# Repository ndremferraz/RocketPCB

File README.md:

# RocketPCB
This repositiory is meant to store my individual work on the PCB for the GW Rocket Team. The code and other documentation is contained in the main repository for the GW Rocket Team

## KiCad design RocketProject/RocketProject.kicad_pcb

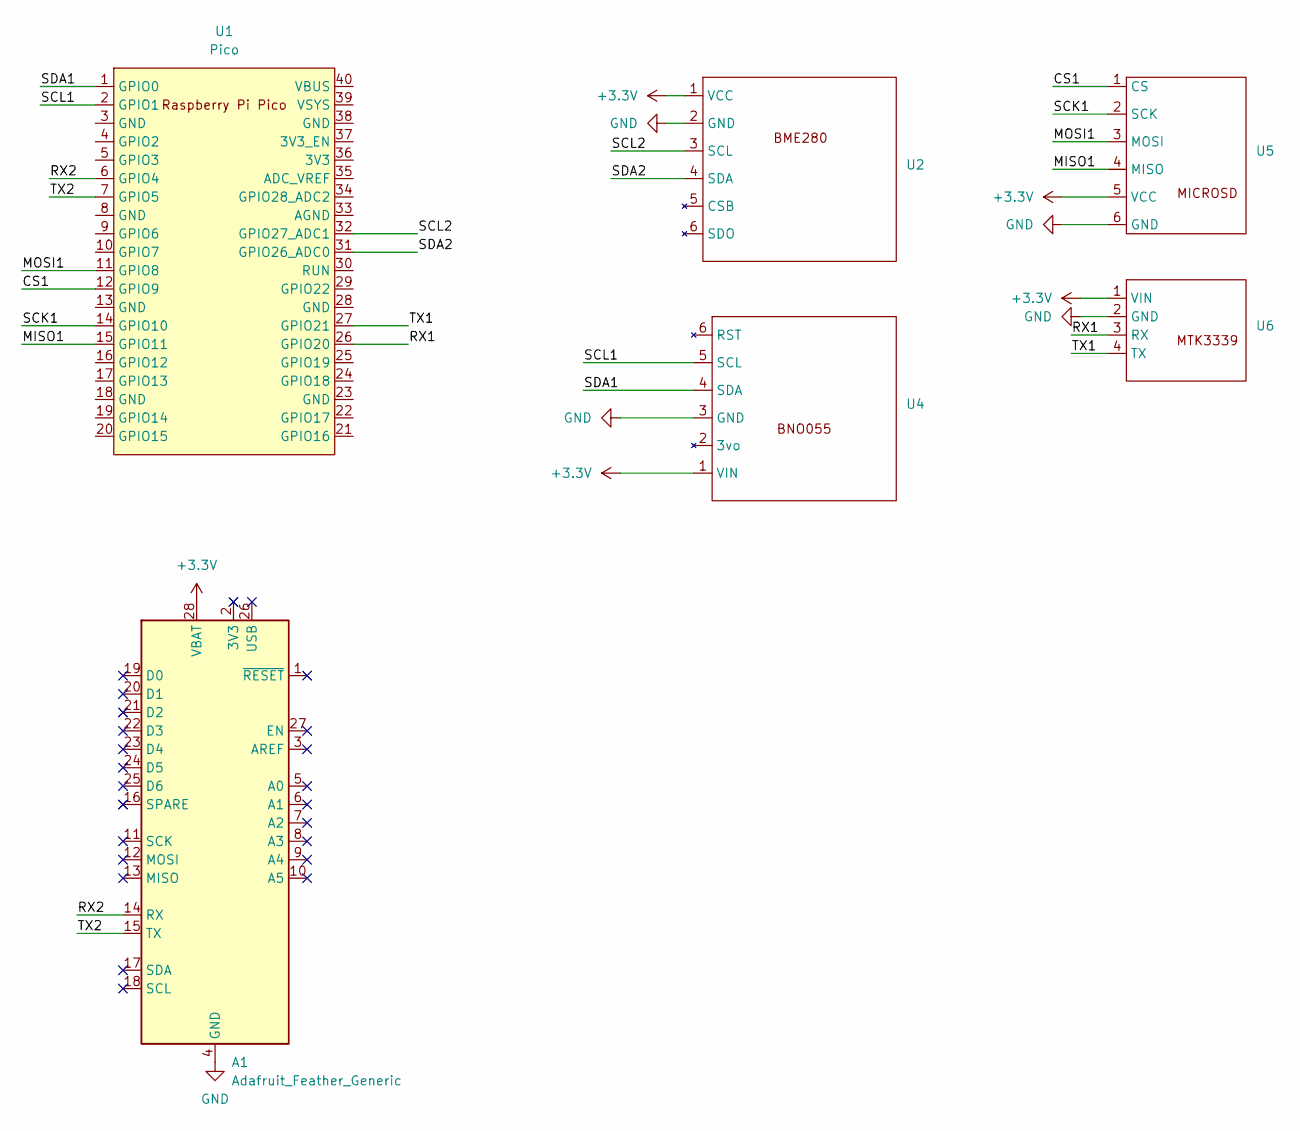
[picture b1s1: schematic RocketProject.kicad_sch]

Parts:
A1: Adafruit_Feather_Generic; Adafruit_Feather
U1: Pico; RaspberryPi_Pico_Common_THT
U2: BME280
U4: BNO055
U5: MICROSD
U6: MTK3339

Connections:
+3.3V: A1.28 (VBAT), U2.1 (VCC), U4.1 (VIN), U5.5 (VCC), U6.1 (VIN)
/CS1: U1.12 (GPIO9), U5.1 (CS)
/MISO1: U1.15 (GPIO11), U5.4 (MISO)
/MOSI1: U1.11 (GPIO8), U5.3 (MOSI)
/RX1: U1.26 (GPIO20), U6.3 (RX)
/RX2: A1.14 (RX), U1.6 (GPIO4)
/SCK1: U1.14 (GPIO10), U5.2 (SCK)
/SCL1: U1.2 (GPIO1), U4.5 (SCL)
/SCL2: U1.32 (GPIO27_ADC1), U2.3 (SCL)
/SDA1: U1.1 (GPIO0), U4.4 (SDA)
/SDA2: U1.31 (GPIO26_ADC0), U2.4 (SDA)
/TX1: U1.27 (GPIO21), U6.4 (TX)
/TX2: A1.15 (TX), U1.7 (GPIO5)
GND: A1.4 (GND), U2.2 (GND), U4.3 (GND), U5.6 (GND), U6.2 (GND)

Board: 2 copper layers, 6 parts (0 on the bottom side), 14 nets, no tracks yet.

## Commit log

2025-02-27 Adding all KiCAD files
